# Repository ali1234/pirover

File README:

Construction plans for pirover

See https://hackaday.io/project/10836-pirover

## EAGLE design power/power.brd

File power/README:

This folder contains the schematics for the power PCB in Eagle format.

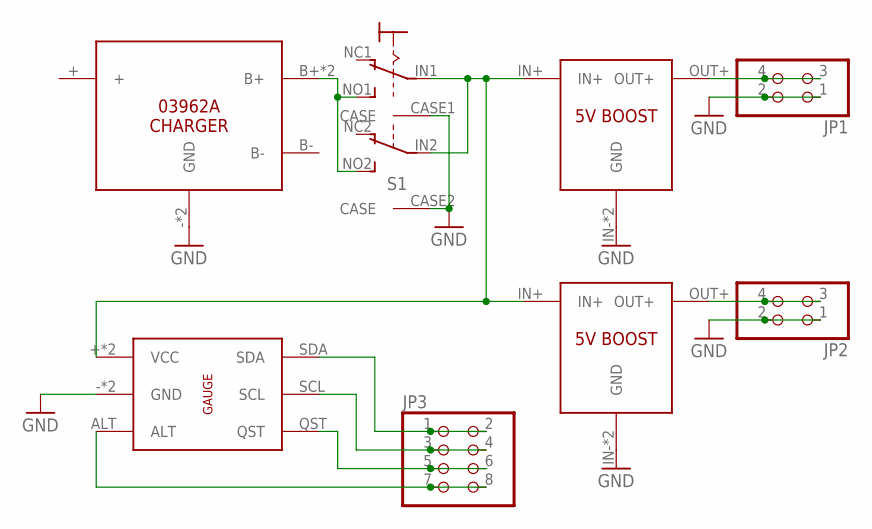
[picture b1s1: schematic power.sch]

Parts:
JP1, JP2: PINHD-2X2/90; 2X02/90
JP3: PINHD-2X4/90; 2X04/90
S1: PUSHSWITCH
U$1: 03962A
U$2, U$3: 5VBOOST
U$4: GAUGE

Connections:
GND: JP1.1, JP1.2, JP2.1, JP2.2, S1.CASE1 (CASE), S1.CASE2 (CASE), U$1.- (GND), U$1.OUT- (GND), U$2.IN- (GND), U$2.OUT- (GND), U$3.IN- (GND), U$3.OUT- (GND), U$4.- (GND), U$4.GND
unnamed: S1.NO1 (NO), S1.NO2 (NO), U$1.B+, U$1.OUT+ (B+)
unnamed: S1.IN1 (IN), S1.IN2 (IN), U$2.IN+, U$3.IN+, U$4.+ (VCC), U$4.VCC
unnamed: JP3.3, JP3.4, U$4.SCL
unnamed: JP3.1, JP3.2, U$4.SDA
unnamed: JP3.7, JP3.8, U$4.ALT
unnamed: JP1.3, JP1.4, U$2.OUT+
unnamed: JP2.3, JP2.4, U$3.OUT+
unnamed: JP3.5, JP3.6, U$4.QST

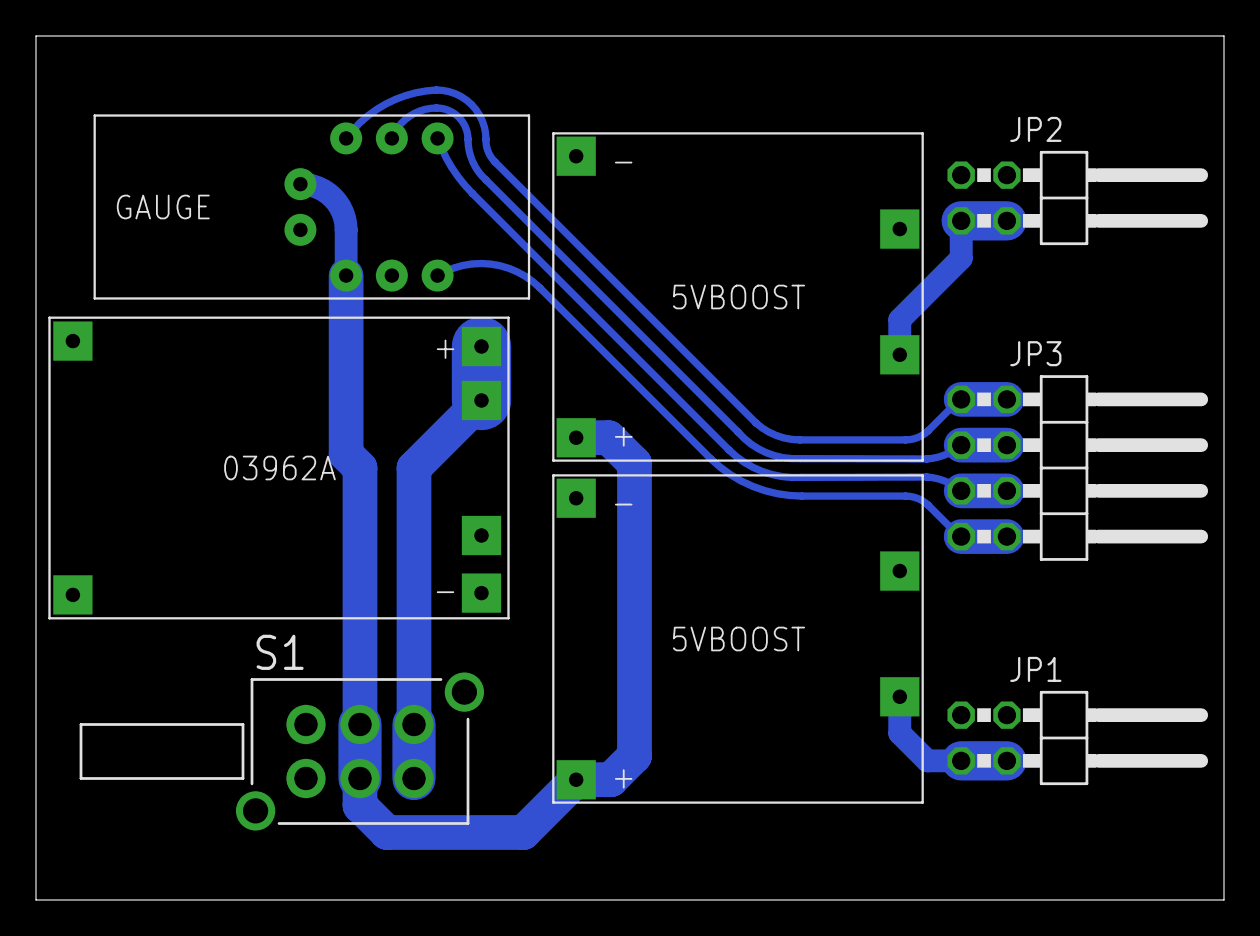
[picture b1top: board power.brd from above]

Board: 2 copper layers, 66.0 x 48.0 mm, 8 parts (0 on the bottom side), 9 nets.

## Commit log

2015-05-27 Construction plans for pirover
2015-05-27 License and README
2017-03-29 Updates to brick plans, and convert to standard LDraw format.
2017-06-21 Update bricks for instruction generator.
2017-07-23 Update instructions with some custom parts.
2017-07-23 Add link to hackaday in README
2017-07-24 Add notes on what the design files actually are.
